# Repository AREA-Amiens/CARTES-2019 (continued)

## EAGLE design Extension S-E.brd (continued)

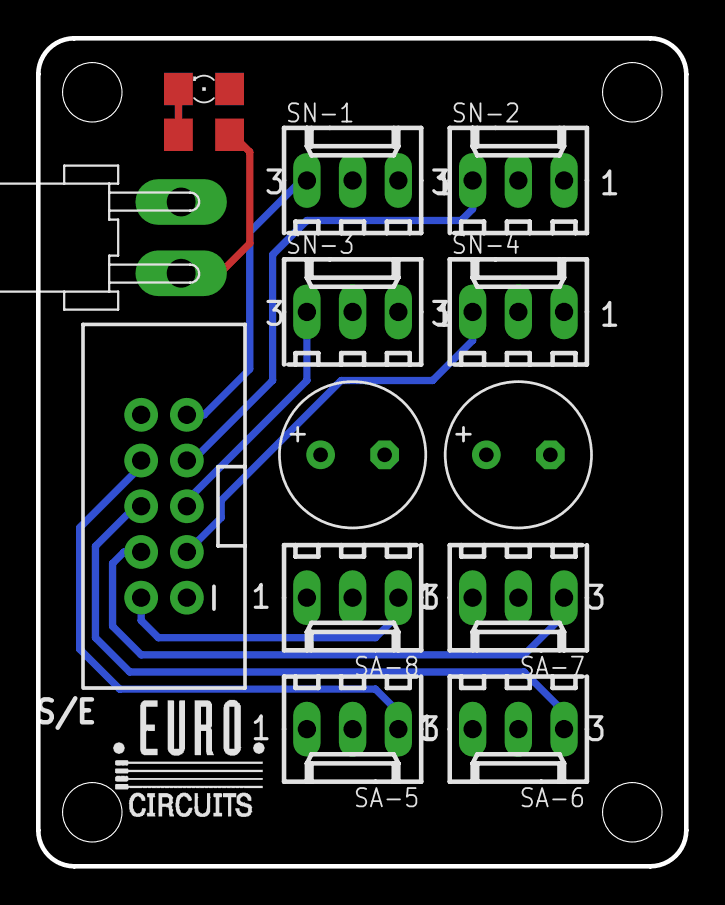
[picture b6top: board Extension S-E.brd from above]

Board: 2 copper layers, 36.0 x 46.0 mm, 14 parts (0 on the bottom side), 11 nets.

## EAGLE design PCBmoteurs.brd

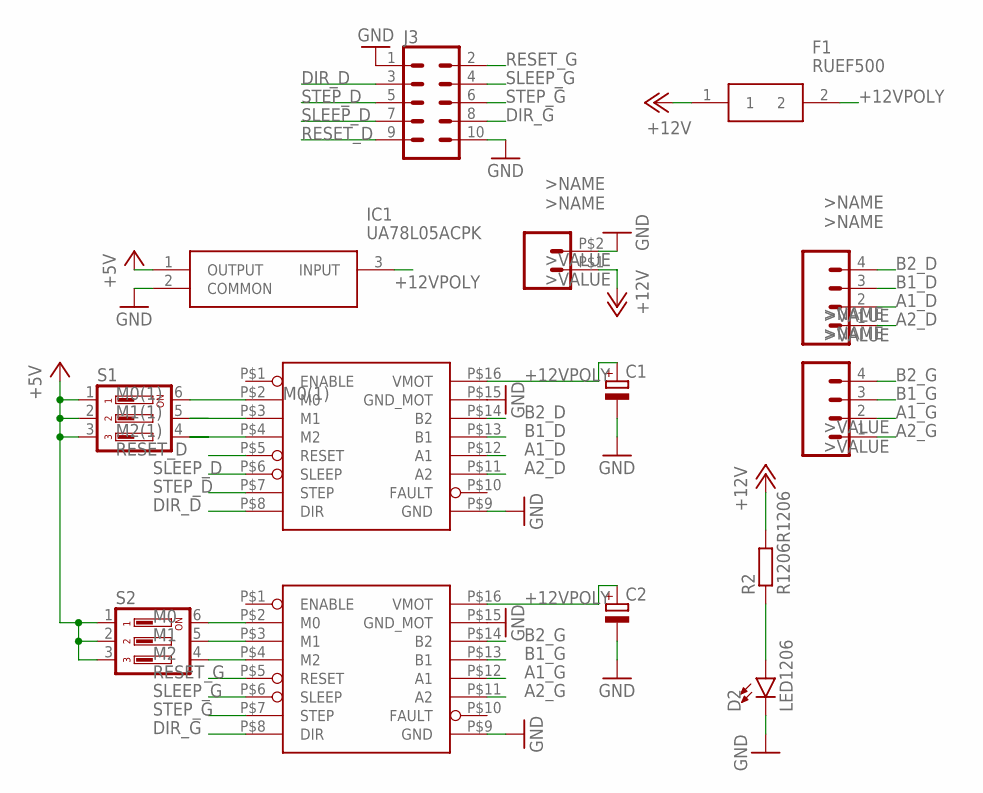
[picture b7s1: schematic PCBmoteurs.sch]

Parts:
C1, C2: CPOL-EUE3.5-8; E3,5-8
D2: LED1206; 1206
F1: RUEF500
IC1: UA78L05ACPK; PK(R-PSSO-F3)
J2: CONN_027A-C; NSK396-2C
J3: CONN_05X2SHD; 2X5-SHROUDED
J4, J6: CONN_04POLAR; MOLEX-1X4
R2: R1206R1206; R1206
S1, S2: DS03; DS-03
U$1, U$2: DRV8825; DRIVER_CARRIER_POLOLU_16

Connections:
+5V: IC1.1 (OUTPUT), S1.1, S1.2, S1.3, S2.1, S2.2, S2.3
+12V: F1.1, J2.P$1 (1), R2.2
+12VPOLY: C1.+, C2.+, F1.2, IC1.3 (INPUT), U$1.P$16 (VMOT), U$2.P$16 (VMOT)
A1_D: J4.2, U$1.P$12 (A1)
A1_G: J6.2, U$2.P$12 (A1)
A2_D: J4.1, U$1.P$11 (A2)
A2_G: J6.1, U$2.P$11 (A2)
B1_D: J4.3, U$1.P$13 (B1)
B1_G: J6.3, U$2.P$13 (B1)
B2_D: J4.4, U$1.P$14 (B2)
B2_G: J6.4, U$2.P$14 (B2)
DIR_D: J3.3, U$1.P$8 (DIR)
DIR_G: J3.8, U$2.P$8 (DIR)
GND: C1.-, C2.-, D2.C, IC1.2 (COMMON), J2.P$2 (2), J3.1, J3.10, U$1.P$9 (GND), U$1.P$15 (GND_MOT), U$2.P$9 (GND), U$2.P$15 (GND_MOT)
M0: S2.6, U$2.P$2 (M0)
M0(1): S1.6, U$1.P$2 (M0)
M1: S2.5, U$2.P$3 (M1)
M1(1): S1.5, U$1.P$3 (M1)
M2: S2.4, U$2.P$4 (M2)
M2(1): S1.4, U$1.P$4 (M2)
unnamed: D2.A, R2.1
RESET_D: J3.9, U$1.P$5 (RESET)
RESET_G: J3.2, U$2.P$5 (RESET)
SLEEP_D: J3.7, U$1.P$6 (SLEEP)
SLEEP_G: J3.4, U$2.P$6 (SLEEP)
STEP_D: J3.5, U$1.P$7 (STEP)
STEP_G: J3.6, U$2.P$7 (STEP)

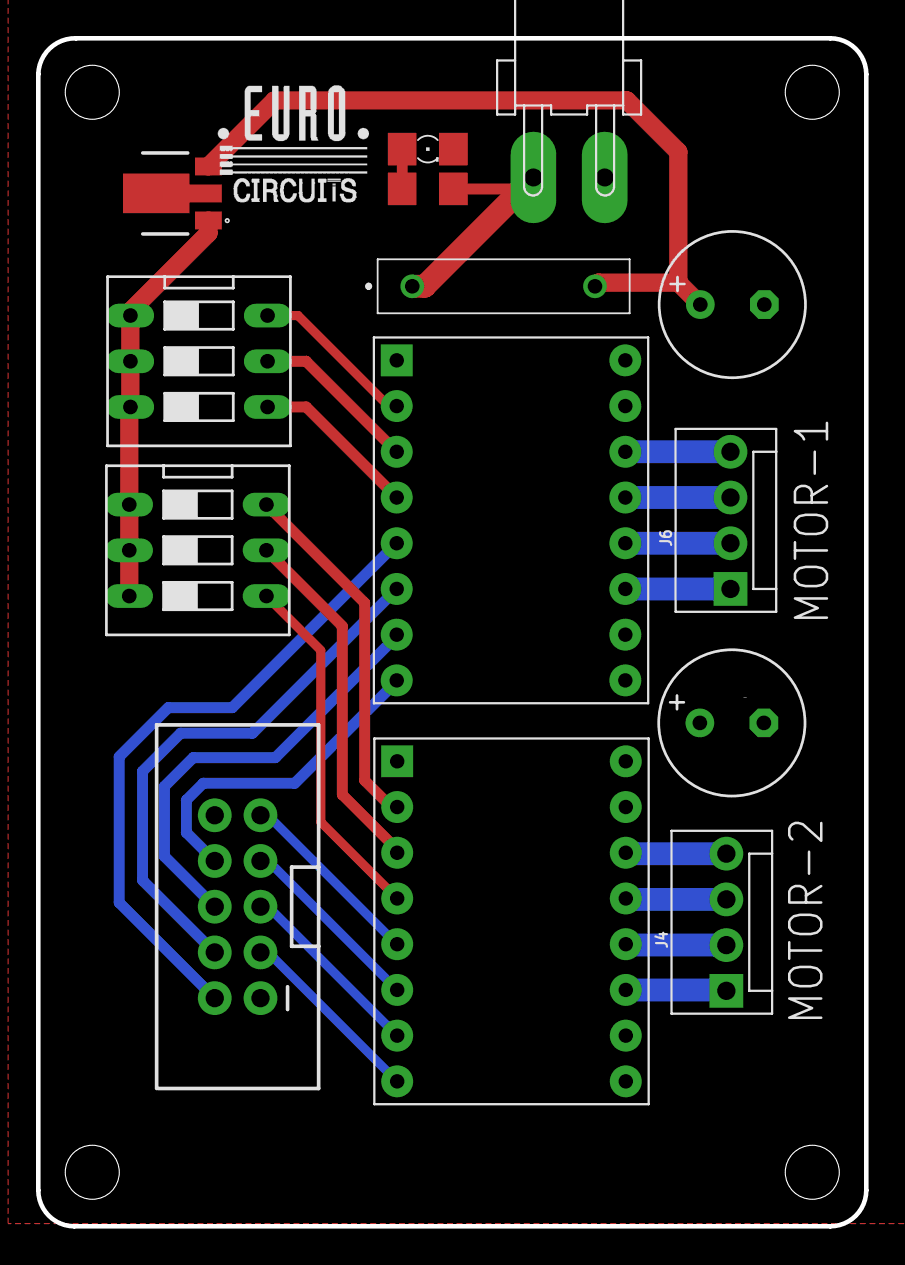
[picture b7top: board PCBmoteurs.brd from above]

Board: 2 copper layers, 46.0 x 66.0 mm, 14 parts (0 on the bottom side), 27 nets.

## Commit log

2019-10-19 Clean
